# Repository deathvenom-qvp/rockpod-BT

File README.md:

<p align="center">
  
  <h1 align="center">Rockpod</h1>
  <p align="center">
    Custom Rockbox firmware for iPod Classic and iPod Video.<br>
    MFi digital audio, Cover Flow, dynamic colors.
  </p>
  <p align="center">
    
    <br/>
    
  </p>
</p>

---

## About This Fork: USB-C + Bluetooth for iPod Classic and iPod Video

> **Status: planning / early development.** Nothing below is implemented yet. Everything else in this README describes upstream [Rockpod](https://github.com/nuxcodes/rockpod) and still applies.

This fork adds firmware support for a hardware mod. The mod replaces the iPod's 30-pin dock connector with a custom board that carries a USB-C port and a built-in Bluetooth audio transmitter.

### Target iPods

| Model                    | Rockbox target | Notes                                                                 |
| ------------------------ | -------------- | --------------------------------------------------------------------- |
| iPod Classic 7G          | `ipod6g`       | Primary development target                                            |
| iPod Classic 6G / 6.5G   | `ipod6g`       | Same build and chips as 7G; board fit in thick/thin cases to confirm  |
| iPod Video 5G / 5.5G     | `ipodvideo`    | Separate serial shim needed; plastic front allows better antenna range |

The board solders onto the original 30-pin pads. USB, power, audio and control all come from those pads, so there is no other soldering to the logic board. That keeps the install simple and reversible.

### Hardware

| 30-pin pad   | Signal               | Goes to                               |
| ------------ | -------------------- | ------------------------------------- |
| 23, 25, 27   | USB VBUS, D−, D+     | USB-C receptacle (charging + sync)    |
| 18           | 3.3V accessory power | Bluetooth module supply               |
| 12 / 13      | Serial TX / RX       | Bluetooth module UART RX / TX         |
| 3 / 4        | Line out R / L       | Bluetooth module analog input         |
| 2            | Audio ground         | Bluetooth module audio reference      |
| 1, 15, 16, 29, 30 | Ground          | Board ground                          |

- **Bluetooth module:** Feasycom FSC-BT1046 (Qualcomm QCC3056, 12.4 × 12.4 mm, aptX), small enough for a one-piece board. Fallback: FSC-BT1035 (same chip, 26.9 × 13 mm, needs a rigid-flex board). Both are A2DP Source modules controlled by AT commands over UART.
- **Schematic and PCB (v0.1 draft):** [`hardware/pcb`](hardware/pcb) has a KiCad 8 project for EasyEDA Pro import: the full schematic and a placed, not yet routed, 2-layer L-shaped board with every part on top. Two footprints are placeholders until checked against the parts bought.
- **Attach and audio design:** [`hardware/DESIGN.md`](hardware/DESIGN.md). The board solders onto the receptacle's pads: castellated edges on the two shield tabs, and a bottom-side pad row for the signals (only the pins we use), left partly exposed so a fine-tip iron can reflow it. Audio ground (pin 2) stays isolated from GND, and each audio channel runs as a pseudo-differential pair with an RF filter.
- **30-pin reference CAD:** [`hardware/reference/ipod-30pin`](hardware/reference/ipod-30pin) has the receptacle's footprint and symbol for Eagle and KiCad, from SparkFun's library. Still to be checked against a real logic board.
- **Parts list:** [`hardware/BOM.csv`](hardware/BOM.csv), in JLCPCB assembly format. Estimated parts cost is about $12 per board, almost all of it the Bluetooth module.
- **USB-C:** 5.1 kΩ pull-downs on CC1/CC2 so USB-C chargers supply power. Data stays USB 2.0.
- **Antenna:** on the 6G/7G, placed at the dock opening, the only gap in the metal case. On the 5G/5.5G, it can face the plastic front instead.
- **No pairing button.** Pairing is done from the Rockbox menu.
- **One PCB for all models** if measurements confirm the pads line up across the 5G, 6G and 7G. Third-party USB-C boards already fit gen 5–7, which suggests they do.

**To verify on real hardware:**
- The current limit of the 3.3V accessory supply on each power chip.
- That the pad positions match across generations.
- How much room there is behind the connector in each case.

### Planned firmware changes

- **Bluetooth menu.** Replaces *System → Accessory Power Supply*. On/off reuses the existing `accessory_supply` setting, which switches pad 18 and powers the module: PMU LDO6 on the 6G/7G, the PCF50605 on the 5G/5.5G. The config name stays the same, so existing settings files keep working.
- **Shared Bluetooth driver.** The driver and menus live in the app layer, so one implementation serves both targets.
- **Per-target serial shims.** On both targets the dock UART is set up for iAP: it waits for an accessory and auto-detects the baud rate. A new build option will open the port at a fixed 115200 8N1 and send data to the Bluetooth driver instead. That means one shim in `serial-6g.c` (6G/7G) and one in `uart-pp.c` (5G/5.5G). iAP over USB (MFi digital audio) is unaffected.
- **Pairing screens:**
  - Scan for nearby devices, showing name and signal strength.
  - Pair and connect.
  - Manage paired devices (connect or forget).
  - Show live connection status from the module's `+A2DPSTAT` events.
- **Line out follows Bluetooth.** Line out is powered on automatically while Bluetooth is on.
- **Volume from the click wheel.** The QCC transmitter AT command set has `AT+ABSVOL`, which sets the headphones' volume directly, so Rockbox can send its volume to the headphones on every model. The module also reports headphone volume buttons (`+CTVOLUP` / `+CTVOLDN`).
- **Later:** use headphone buttons (AVRCP) to control Rockbox playback.

### Roadmap: hardware first

The priority is one board that drops into every supported iPod. Firmware work starts once the hardware is proven.

1. **Measure.** Pad positions, and the room behind the connector, on a 5G, 6G and 7G logic board and case. Design to the tightest one, the thin 7G.
2. **Confirm the module.** Check with Feasycom that the FSC-BT1046 uses the same QCC transmitter AT command set as the FSC-BT1035, and confirm JLCPCB stock.
3. **Bench test.** Drive the module from a USB-to-serial adapter: scan, pair, connect, line-in audio and absolute volume.
4. **Measure pad 18 under load.** On each iPod, check the 3.3V accessory supply holds up while the module pairs and streams.
5. **Prototype the board** and test the fit, the USB-C charging and sync, and the antenna range inside each case.
6. **Firmware.** Write the Bluetooth driver, the serial shims and the menus.

---

Rockpod is a [Rockbox](https://www.rockbox.org) fork for iPod Classic (6th/7th gen, 2007–2014) and iPod Video (5th/5.5th gen, 2005–2006). It adds MFi digital audio output, a rewritten Cover Flow, dynamic album art colors, and SSD-aware power management.

Rockpod supports both HDD and iFlash-modded units. Both iPod models share the same 320x240 display and get the same UI features — Cover Flow, dynamic colors, themes, and rendering improvements. Hardware-specific features like SSD power management and MFi digital audio are iPod Classic only for now. It's a drop-in replacement for the official Rockbox firmware, with no reformatting or data loss.

---

## Features

### Digital Audio Output
> Supported on iPod Classic 6G/7G

Rockpod is the first open source firmware to support digital audio output over the iPod's dock connector. It handles the full Apple iAP authentication handshake, negotiates sample rate with the accessory, and sends bit-perfect PCM over USB, bypassing the iPod's internal DAC. The entire Rockbox DSP chain (EQ, crossfeed, replaygain) is preserved in the output path.

This works with any MFi iPod dock connector accessory — DACs, speakers, docks, car stereos, and other digital audio accessories built for the iPod.

- **Full iAP/IDPS authentication** — certificate exchange, challenge-response, FID token negotiation, Digital Audio Lingo activation
- **3 MB TX ring buffer** — absorbs codec decode bursts and compensates for I2S/USB clock drift (~44,117 Hz vs 44,100 Hz)
- **Double-buffered ISO IN** — DMA re-arm decoupled from audio pull for glitch-free streaming on docks with HID polling
- **Glitch-free transitions** — fade-in on play, fade-out on pause/underflow, buffer flush between tracks
- **Full DSP chain preserved** — EQ, crossfeed, replaygain, stereo width all apply before the USB stream
- **HP amps auto-mute** — CS42L55 headphone amplifiers power down during USB streaming
- **USB-C compatible** — digital audio output also works with USB-C connector mods

None of this existed in Rockbox before. It required building a new protocol stack from scratch: USB Audio Class 1.0 source mode, Apple's iAP/IDPS authentication (certificate exchange, challenge-response, FID token negotiation), a custom iAP-over-USB-HID transport layer, and Digital Audio Lingo to activate streaming.

<details>
<summary><strong>Compatible devices</strong></summary>

Any iPod dock connector accessory that uses Digital Audio Lingo (0x0A) should work. The OPPO HA-2SE is the primary tested device. DACs, speakers, docks, and car stereos that accept digital audio from an iPod are all expected to be compatible.

**DACs**

- OPPO HA-2 / HA-2SE
- Sony PHA-1 / PHA-1A
- Sony PHA-2 / PHA-2A
- Onkyo DAC-HA200
- Denon DA-10
- JDS Labs C5D
- Fostex HP-P1
- Cypher Labs AlgoRhythm Solo / Solo -dB

**Speakers / Docks** — MFi-certified speakers and docks that use digital audio (not analog line-out) over the dock connector should also work.

</details>

<details>
<summary><strong>Under the hood: signal flow</strong></summary>

```
iPod connects via dock USB
    │
    ├─ USB enumeration: Config 2 = UAC1 source + iAP HID (Apple VID/PID 0x05AC:0x1261)
    │
    ├─ iAP authentication over USB HID:
    │     StartIDPS → SetFIDTokenValues → EndIDPS
    │     → MFi certificate exchange → challenge-response
    │
    ├─ Digital Audio Lingo activation:
    │     GetAccSampleRateCaps → TrackNewAudioAttributes @ 44.1 kHz
    │
    ├─ Accessory selects alt-setting on source streaming interface
    │
    └─ Audio path:
          Codec → DSP (EQ, crossfeed, replaygain)
            → PCM mixer → buffer hook → TX ring buffer
              → double-buffered ISO IN → MFi accessory
```

The iAP HID transport handles multi-report fragmentation for large payloads (128-byte RSA signatures span multiple HID reports, reassembled via link control bytes). Transaction IDs are tracked and echoed for all post-IDPS commands.

Key files:

- `firmware/usbstack/usb_audio.c` — source mode streaming engine
- `firmware/usbstack/usb_iap_hid.c` — iAP-over-USB-HID transport (new)
- `firmware/usbstack/usb_core.c` — dual USB configuration
- `apps/iap/iap-lingo0.c` — IDPS protocol, Digital Audio Lingo
</details>

---

### Cover Flow

Stock PictureFlow shows 3 slides, uses hardcoded colors, and is buried in the plugins menu. Rockpod rewrites the renderer to match Apple's Cover Flow — 7 visible slides w/ uniform tilt angle, custom theme integration, status bar toggle, faster transitions — and promotes it to a top-level menu entry.

<!-- TODO: Add before/after screenshot — stock PictureFlow vs Rockpod Cover Flow -->

|                     Cover Flow                     |                        Full-screen mode                         |
| :------------------------------------------------: | :-------------------------------------------------------------: |
|  |  |
|                   Status bar on                    |                     Status bar toggled off                      |

|                          Track list                          |                      Display settings                       |
| :----------------------------------------------------------: | :---------------------------------------------------------: |
|  |  |
|             Title only — no track number prefix              |                Slide tuck, crossfade, speed                 |

- **Theme-aware colors** — slide edges and backgrounds fade toward your theme's background color, not hardcoded black
- **Status bar support** — integrates with the SBS status bar, showing "Cover Flow" in the title bar. Can be toggled off for full-screen mode
- **7 visible slides w/ parallel slide rendering** — matching Apple's Cover Flow projection
- **Configurable transition speed** — scroll and transition speeds are adjustable in display settings
- **Text crossfade** — album and artist text fades smoothly between slides instead of snapping
- **100-slot slide cache** (up from 64), Bayer-ordered dithering, 1-second background polling in SSD mode
- **Track list** shows title only — no "1.03 -" disc/track number prefixes
- **No startup delay** — the 2-second "Loading..." splash is eliminated under SSD mode

---

### Dynamic Colors

The UI automatically extracts dominant and accent colors from the currently playing album art and applies them across all skinnable screens — menus, status bar, and now playing. Colors fade smoothly over 500 ms when the track changes.

|                                                          |                                                          |
| :------------------------------------------------------: | :------------------------------------------------------: |
|        |        |
|        |        |

- **Album art color extraction** — dominant and accent colors pulled from the current track's artwork
- **Full theme color coverage** — foreground, background, selector bar, selector text, selector gradient, and list separators all adapt
- **Smooth transitions** — 500 ms fade between color palettes on track change
- **Contrast enforcement** — accent colors are pushed brighter or darker if insufficient contrast against the dominant color
- **On by default** — can be toggled off under Theme Settings

---

### Storage Mode
> Supported on iPod Classic 6G/7G

Rockpod works with both stock HDDs and iFlash SSD mods. HDD behavior is unchanged from stock Rockbox. When an SSD is detected, Rockpod switches to a lighter sleep strategy — faster wake times, lower idle power draw, and no unnecessary spin-up delays.

| Storage Mode                                         |
| :--------------------------------------------------- |
|  |
| Auto-detect, or manually select HDD / SSD            |

- **Auto-detection** via ATA IDENTIFY heuristics (rotation rate, form factor, TRIM support, CFA compliance)
- **Two-phase idle sleep** — clock-gate after 7 seconds (near-instant wake), then cut AUTOLDO after 30 seconds with backlight off
- **Instant wake from clock-gate** — no bus reset, no re-identify (<5 ms)
- **Pre-wake on backlight** — storage wakes when the screen turns on, ready before you navigate
- **HDD features bypassed** — APM and AAM skipped for SSDs
- **Plugin splash skipped** — no "Loading..." screen when load times are negligible

<details>
<summary><strong>Under the hood: sleep states</strong></summary>

| State           | What happens                                  | Wake time |
| --------------- | --------------------------------------------- | --------- |
| **Active**      | Normal operation                              | —         |
| **Clock-gated** | ATA clock off, flash powered, GPIOs held      | <5 ms     |
| **Deep sleep**  | AUTOLDO cut, GPIOs tri-stated, controller off | ~330 ms   |

Stock HDD behavior: full power-down + re-init at ~530 ms.

Key file: `firmware/target/arm/s5l8702/ipod6g/storage_ata-6g.c`

</details>

---

### Power Management
> Supported on iPod Classic 6G/7G

- **I2S clock gating** — bus clock gated when no audio is playing
- **Codec idle power-down** — CS42L55 enters PDN_CODEC on idle, pop-free resume (master mute → power-down → 200 us settle → unmute)
- **Smart charger detection** — LTC4066 `!CHRG` pin sampled with backlight-gated timing and 500 ms settle to distinguish real chargers from weak USB sources like MFi accessories
- **Charge gate** — GPIO C1 blocks battery charging when USB can't deliver 500 mA, preventing accessory battery drain
- **Auto-poweroff with USB** — device shuts down after idle timeout even with non-charging USB connected (stock blocks poweroff indefinitely on any USB)
- **iAP idle tick** — polling drops from 10 Hz to 1 Hz after auth, saving ~9 CPU wakeups/sec

<details>
<summary><strong>Under the hood: LTC4066 charge control</strong></summary>

| GPIO      | Function          | Rockpod behavior                       |
| --------- | ----------------- | -------------------------------------- |
| B6 (HPWR) | USB current limit | LOW = 100 mA, HIGH = 500 mA            |
| B7 (SUSP) | USB suspend       | Prevents any USB power draw            |
| C1        | Charge disable    | HIGH blocks charging from weak sources |

When connected to an MFi accessory without a power bank, C1 goes HIGH during backlight-off to block trickle drain. On backlight-on, C1 goes LOW to sample `!CHRG` — if charging is detected, it stays LOW.

Key files: `firmware/target/arm/s5l8702/ipod6g/power-6g.c`, `powermgmt-6g.c`

</details>

---

### Menu

All standard Rockbox menu items are available.

|                     Main menu                     |                    Database track list                     |
| :-----------------------------------------------: | :--------------------------------------------------------: |
|  |  |
|       Full menu available, shown customized        |         Title only — no disc/track number clutter          |

---

### Improved UI Rendering

- **Scroll-to-start flash eliminated** — custom themes with scrolling text in the main menu would flash or flicker when the scroll position reset to the start. Rockpod fixes the viewport rendering order to prevent this, making themed menus render cleanly without visual artifacts.
- **Track name cleanup** — strips the "01 " numeric prefix that iTunes sync adds to filenames, so tracks display by their actual title across Cover Flow, Database, and WPS

---

### Bundled Themes

The repo includes third-party themes under `themes/`:

- **adwaitapod_dark_simplified** — modified with swapped play/pause button icons. Original by [Dook](https://github.com/D0-0K/adwaitapod) (CC-BY-SA). Theme zip available in the [v2.0 release](https://github.com/nuxcodes/rockpod/releases/tag/v2.0).
- **Themify 2** — modified with corrected menu text centering. Original by [Dook](https://github.com/D0-0K/themify).

---

## Supported Models

| Feature                   | iPod Classic (6G/7G)  | iPod Video (5G/5.5G) |
| ------------------------- | --------------------- | -------------------- |
| **MFi digital audio**     | Yes                   | Planned              |
| **Cover Flow**            | Yes                   | Yes                  |
| **Dynamic Colors**        | Yes                   | Yes                  |
| **UI improvements**       | Yes                   | Yes                  |
| **Themes**                | Yes (320x240)         | Yes (320x240)        |
| **SSD power management**  | Yes                   | No                   |
| **Advanced power mgmt**   | Yes                   | No                   |

## At a Glance

|                         | Stock Rockbox                           | Rockpod                                        |
| ----------------------- | --------------------------------------- | ---------------------------------------------- |
| **MFi digital audio**   | Not supported                           | DACs, speakers, docks — Classic only           |
| **Dynamic colors**      | Not supported                           | Album art color extraction with smooth fades   |
| **Cover Flow**          | 3 slides, no status bar, 70-degree tilt | 7 slides, status bar, parallel projection      |
| **SSD idle**            | Full power-down, ~530 ms wake           | Clock-gate, <5 ms wake — Classic only          |
| **Codec power**         | Always on                               | Auto power-down on idle — Classic only         |
| **USB power**           | Charges from any USB source             | Smart charge gating — Classic only             |
| **Auto-poweroff + USB** | Blocked indefinitely                    | Works for non-charging accessories — Classic only |

---

## Installation

> **Prerequisite:** Your iPod must already have the Rockbox bootloader installed. See the [Rockbox installation guide](https://www.rockbox.org/wiki/RockboxUtility) if needed.

1. Download the correct zip from [Releases](https://github.com/nuxcodes/rockpod/releases/latest):
   - `rockbox-ipod6g.zip` for iPod Classic (6G/7G)
   - `rockbox-ipodvideo-5g.zip` for iPod Video (5G/5.5G)
2. Connect your iPod in disk mode
3. Extract the zip to the root of the iPod (creates/updates `.rockbox`)
4. Eject and reboot

PictureFlow rebuilds its album art cache on first launch after upgrade. This is automatic.

---

## Building from Source

```bash
# iPod Classic 6G (default, clean build)
./build-hw.sh

# iPod Video 5G (clean build)
./build-hw.sh 5g

# Incremental rebuild
cd build-hw-ipod6g && make -j$(sysctl -n hw.ncpu) && make zip
cd build-hw-ipodvideo && make -j$(sysctl -n hw.ncpu) && make zip

# Simulator (6G)
./build-sim.sh
cd build-sim && ./rockboxui
```

`build-hw.sh` accepts `ipod6g` / `6g` (default) or `ipodvideo` / `5g`. Output goes to `build-hw-<target>/`. Cross-compiler toolchains: `tools/rockboxdev.sh`.

---

## Roadmap

**iPod Video 5G/5.5G MFi digital audio.** Master supports serial iAP and analog line-out on iPod Video, but does not advertise Digital Audio because its USB audio transport is not enabled. The experimental USB work remains on the separate `ipod5g-mfi-usb` branch.

**Generic USB audio support via host mode.** The current support uses USB device mode — the accessory is the host and the iPod authenticates as an Apple audio source. This only works with iPod MFi accessories. The next step is USB host mode, where the iPod becomes the host and sends audio to any class-compliant UAC device — standard USB-C DAC dongles via a dock-to-OTG adapter. The S5L8702's DWC OTG controller supports host mode in hardware; the work is in the host stack and UAC class driver.

---

## Known Limitations

- **iPod MFi accessories only** — generic UAC sinks not yet supported (see Roadmap)
- **16-bit PCM, 44.1 / 48 kHz** — USB Audio Class 1.0 ceiling
- **iPod Classic and iPod Video only** — untested on other Rockbox targets
- **No USB DAC (sink) mode** — USB audio config is repurposed for digital audio output
- **Rockbox bootloader required** — needs an existing Rockbox installation

---

## Credits

Built on the work of the [Rockbox](https://www.rockbox.org/) project and its contributors.

- **Themes:** adwaitapod_dark_simplified and Themify 2 by [Dook](https://github.com/D0-0K) (CC-BY-SA)
- **MFi reference:** [ipod-gadget](https://github.com/oandrew/ipod-gadget) descriptor layout, [rockbox-mojyack](https://github.com/mojyack/rockbox) iPod 5G iAP implementation, Apple MFi Accessory Firmware Specification

## License

[GNU General Public License v2.0](https://www.gnu.org/licenses/old-licenses/gpl-2.0.html)

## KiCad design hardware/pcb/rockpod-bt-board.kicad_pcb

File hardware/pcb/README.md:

# Unified board v0.1: schematic and first-pass layout

KiCad 8 project for EasyEDA Pro import: the complete schematic and a placed (not yet routed) 2-layer PCB. All parts are SMD on the top side. The underside carries only the pads that solder to the iPod.

> **Draft for review, not for ordering.** Two footprints are placeholders (see "Assumptions"), and the geometry has to be checked against measured iPods (roadmap step 1). Routing comes after both are settled.

## Files

| File | What it is |
| --- | --- |
| `rockpod-bt-board.kicad_sch` | Full schematic. Nets connect by label name. Every part has an `LCSC` / `Supplier Part` field. |
| `rockpod-bt-board.kicad_pcb` | Board outline, placed footprints with nets (ratsnest), iPod interface pads, shield tabs, alignment holes, top GND pour and antenna keep-out. |
| `rockpod-bt-board.kicad_pro` | Project file. |
| `board-preview.png` | Plot of the placement. |
| `tools/` | Python generator. Edit `design.py` (geometry, parts, placement) and rerun to regenerate everything. |

## Importing into EasyEDA Pro

1. *File → Import → KiCad*, and select `rockpod-bt-board.kicad_pro` (or the `.kicad_sch` and `.kicad_pcb`).
2. **Replace U1 and J1 with EasyEDA library parts:**
   - U1: search `C9900132912` (FSC-BT1046).
   - J1: search `C5187472` (SHOU HAN TYPE-C 16P QTWT).

   Then *Update PCB from schematic*. Every other footprint is a standard 0402, 0603, SOT-23-6 or 1206 land pattern.
3. Check the board against the "Assumptions" list, then route with the rules below.

## Board

- **2 layers, 0.8 mm FR4.** 36.5 × 20.8 mm, L-shaped.
- **Main strip** sits in the 30-pin receptacle's place. It carries the USB-C port, USB ESD protection, the CC resistors and the audio front end.
- **Extension** reaches back into the case on one side only, as decided, to stay clear of the logic board's other connectors. It carries the Bluetooth module, its supply parts, the RF filter and the antenna. Everything sits in `design.py`, so it can be mirrored to the other side once the iPods are measured.
- **Rear edge over the pad row** stops 0.125 mm past the pad centreline, leaving the rear 0.75 mm of each iPod pad exposed for a fine-tip iron.
- **Underside pads run flush to that rear edge** (0.28 × 1.0 mm), so solder flows straight from the exposed iPod pad onto ours. This breaks the usual 0.2 mm copper-to-edge rule on purpose:
  - Mark it as accepted in EasyEDA's DRC.
  - Add an order note for JLCPCB not to trim the bottom pads on the rear edge.
- **Shield tabs:** tab 31 (left) is castellated on the board edge. Tab 32 (right) falls inside the extension, so it gets a plated slot instead, which solder fed from the top flows through.
- **Alignment holes:** two 1.1 mm holes match the iPod's receptacle locating holes at x = ±6.25 mm.
- **Antenna (internal, ceramic chip, in the dock opening):** the module has no antenna of its own. The FSC-BT1046 datasheet says to connect a 50 Ω antenna to RF_IO (pin 7).
  - **Placement:** ANT1, a 3.2 × 1.6 mm ceramic chip, sits at the front edge beside the USB-C, inside the old 30-pin opening. On the 6G/7G that opening, behind the plastic bezel insert, is the only gap in the metal case.
  - **Keep-out:** an area of about 5 × 3 mm around ANT1 has no copper on either layer.
  - **Matching:** the pi-match sits right beside the antenna. R9 is fitted with 0 Ω; C10 and C11 are left unfitted for tuning.
  - **Feed line:** RF_MOD runs from module pin 7 to the pi-match as a 50 Ω coplanar line.
  - **Watch:** the iPod logic board under the old receptacle may carry a ground plane right below the antenna, which will detune it. Plan to tune C10/C11 with the board installed.

## Assumptions to check first

1. **U1 pin 1 position.** The FSC-BT1046 datasheet's text gives the pin table, the 1.0 mm pitch and the 12.4 mm body, but not where pin 1 sits. This footprint assumes pin 1 at the front-left corner, numbered counter-clockwise. The EasyEDA library footprint for C9900132912 settles it, and parts around the module may need to move once it's in.
2. **J1 is the SHOU HAN TYPE-C 16P QTWT (C5187472):** a 16-pin USB-C receptacle that LCSC lists as fully surface-mount, with no through-hole shell legs, 7.35 mm long. It replaces the HRO TYPE-C-31-M-12 and G-Switch GT-USB-7010ASV, which both have through-hole shell legs. The J1 footprint here is a generic 16-pin pattern, so use the EasyEDA library footprint.
3. **USB-C depth.** A USB-C receptacle is about 7.35 mm long. The 30-pin body was about 6.6 mm deep, and the board can't run past the pad row. So the USB-C mouth sits 0.45 mm proud of the board front, about 0.6 mm past where the 30-pin mouth was. Check that against the case opening.
4. **Case clearance.** Check the extension (x = 9 to 24.8 mm, y up to 14 mm behind the pad row) against parts on the logic board and the curve of the case corner.
5. **Pad positions.** The iPod pad row comes from SparkFun's footprint. The contact row in the 3D model in `../reference/ipod-30pin/3d` agrees: 30 tails at 0.5 mm pitch, centred ±7.25 mm.
6. **Shield tabs are ground,** on each generation.

## Routing rules

- **AGND (iPod pin 2) never touches GND.** Keep it off the ground pour. It splits into two return traces, one for each audio pair.
- **Audio pairs:**
  - Route LINE_L/AGND → R5/R6 → C6/C7 → AUD_L_P/AUD_L_N, and LINE_R/AGND → R7/R8 → C8/C9 → AUD_R_P/AUD_R_N, as tightly coupled pairs of about equal length, each pair kept apart from the other.
  - C12 and C13 go right at the module pins.
  - Keep the pairs away from USB D+/D−, RF_MOD/RF_ANT and the antenna.
- **USB D+/D−:** a 90 Ω differential pair from J1 through U2 to the iPod pads 25/27, kept short.
- **iPod interface pads (underside):** USB-C pads sit directly above several of them. Fan the bottom pads out on the bottom layer first, then via up to the top clear of J1's pads. Vias under the USB-C body must be tented.
- **Underside copper:** don't pour on the bottom layer, since it sits on the iPod logic board. Keep bottom traces short and under solder mask.
- **RF:** RF_MOD from module pin 7 to C10/R9/C11 beside the antenna, as a 50 Ω coplanar line over the top ground pour, stitched with GND vias. Keep it clear of the audio pairs and USB D+/D−. No copper of either layer inside the antenna keep-out.
- **Power:** VACC (pad 18) to C1/C2 (bulk) and C3 (VBAT) / C4 (PIO_POWER) close to the module pins.
- **Checks after soldering:** see `../DESIGN.md`.

## Regenerating

```bash
cd hardware/pcb/tools
python3 gen.py ..                      # writes the .kicad_sch / .kicad_pcb / .kicad_pro, prints clearance checks
python3 validate.py ..                 # parses the files, cross-checks schematic vs PCB nets
python3 render.py ../board-preview.png
```

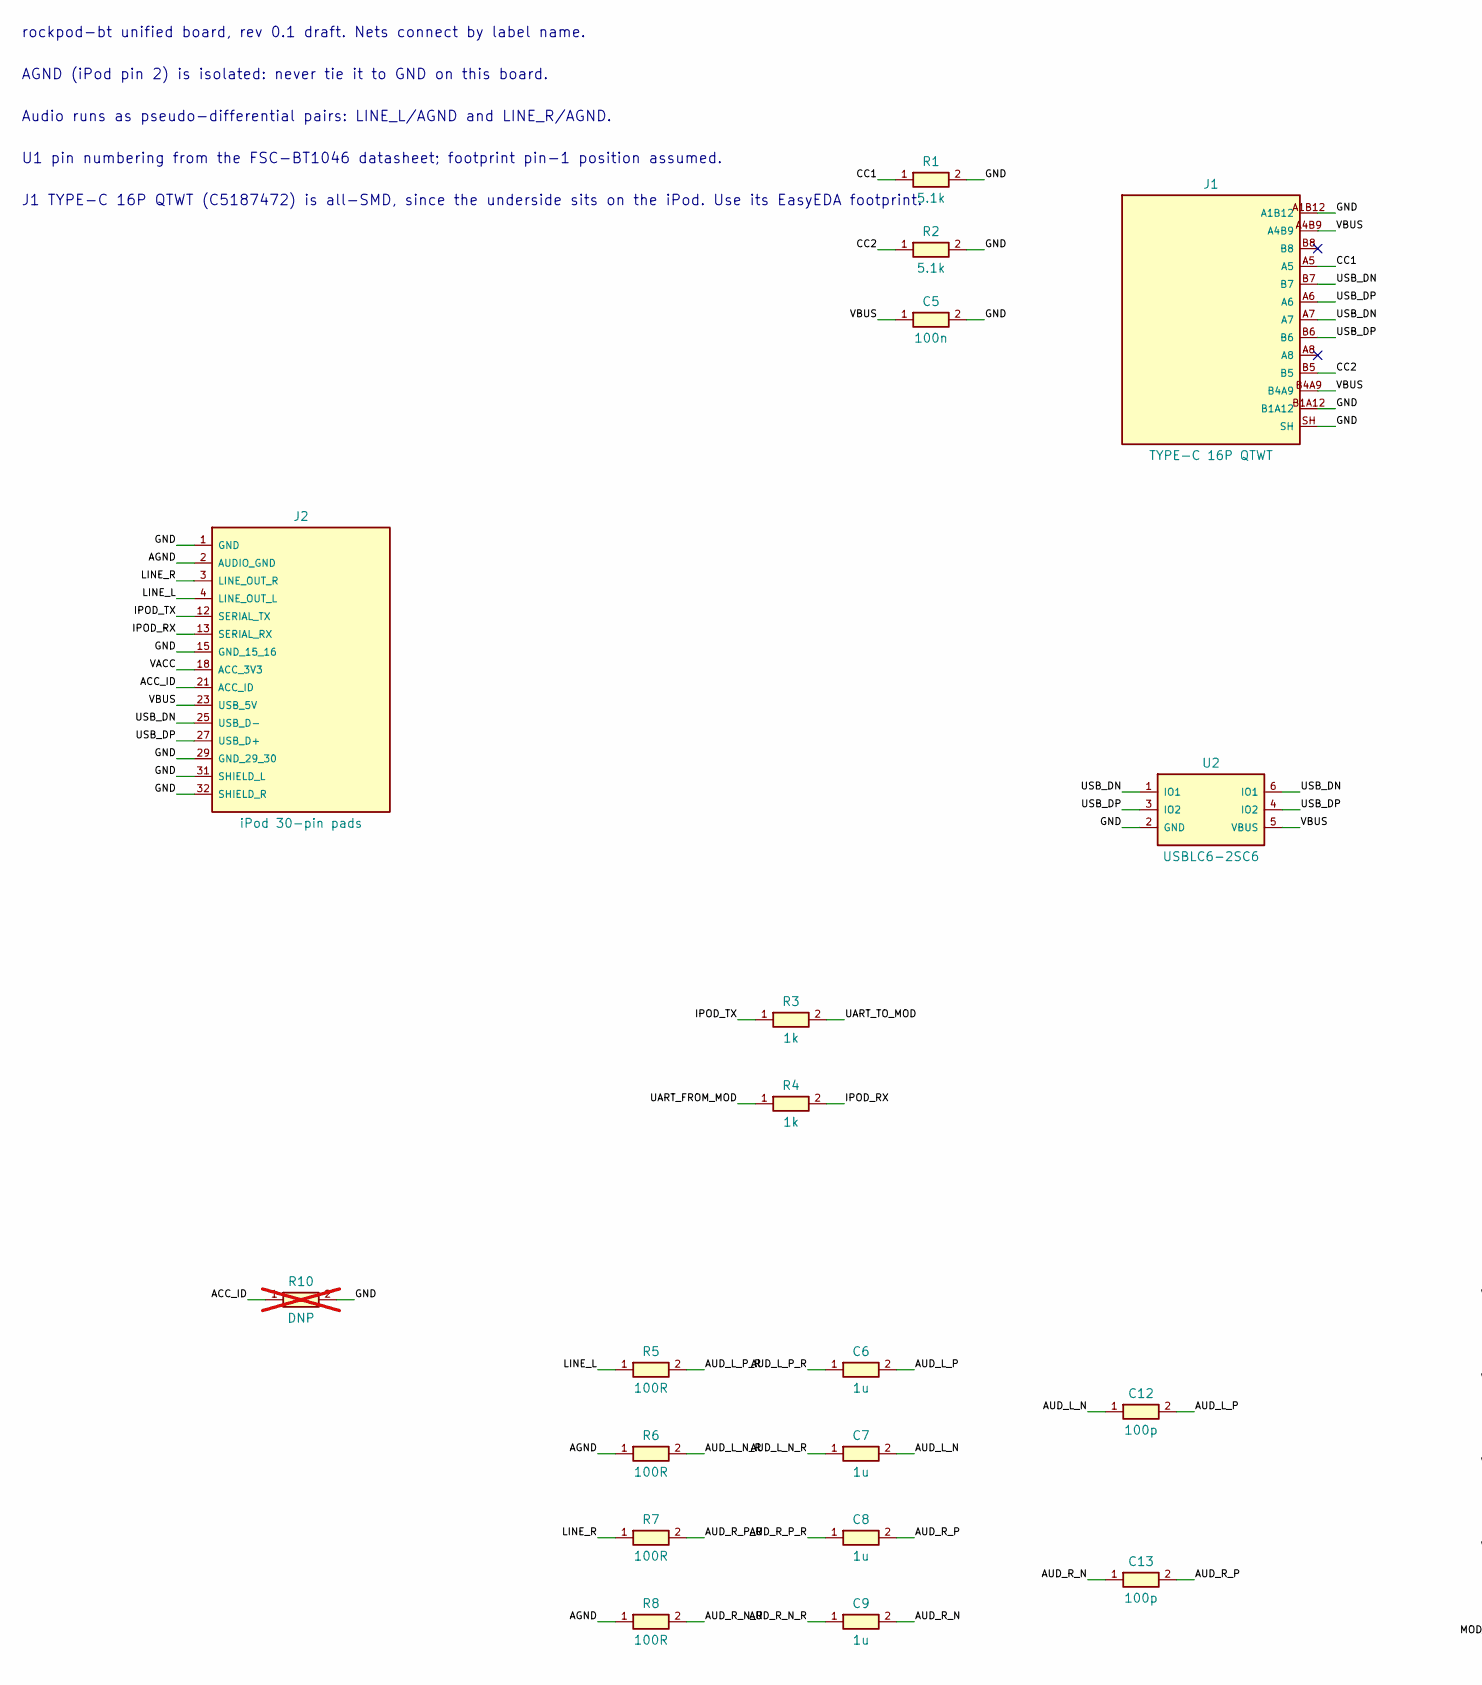
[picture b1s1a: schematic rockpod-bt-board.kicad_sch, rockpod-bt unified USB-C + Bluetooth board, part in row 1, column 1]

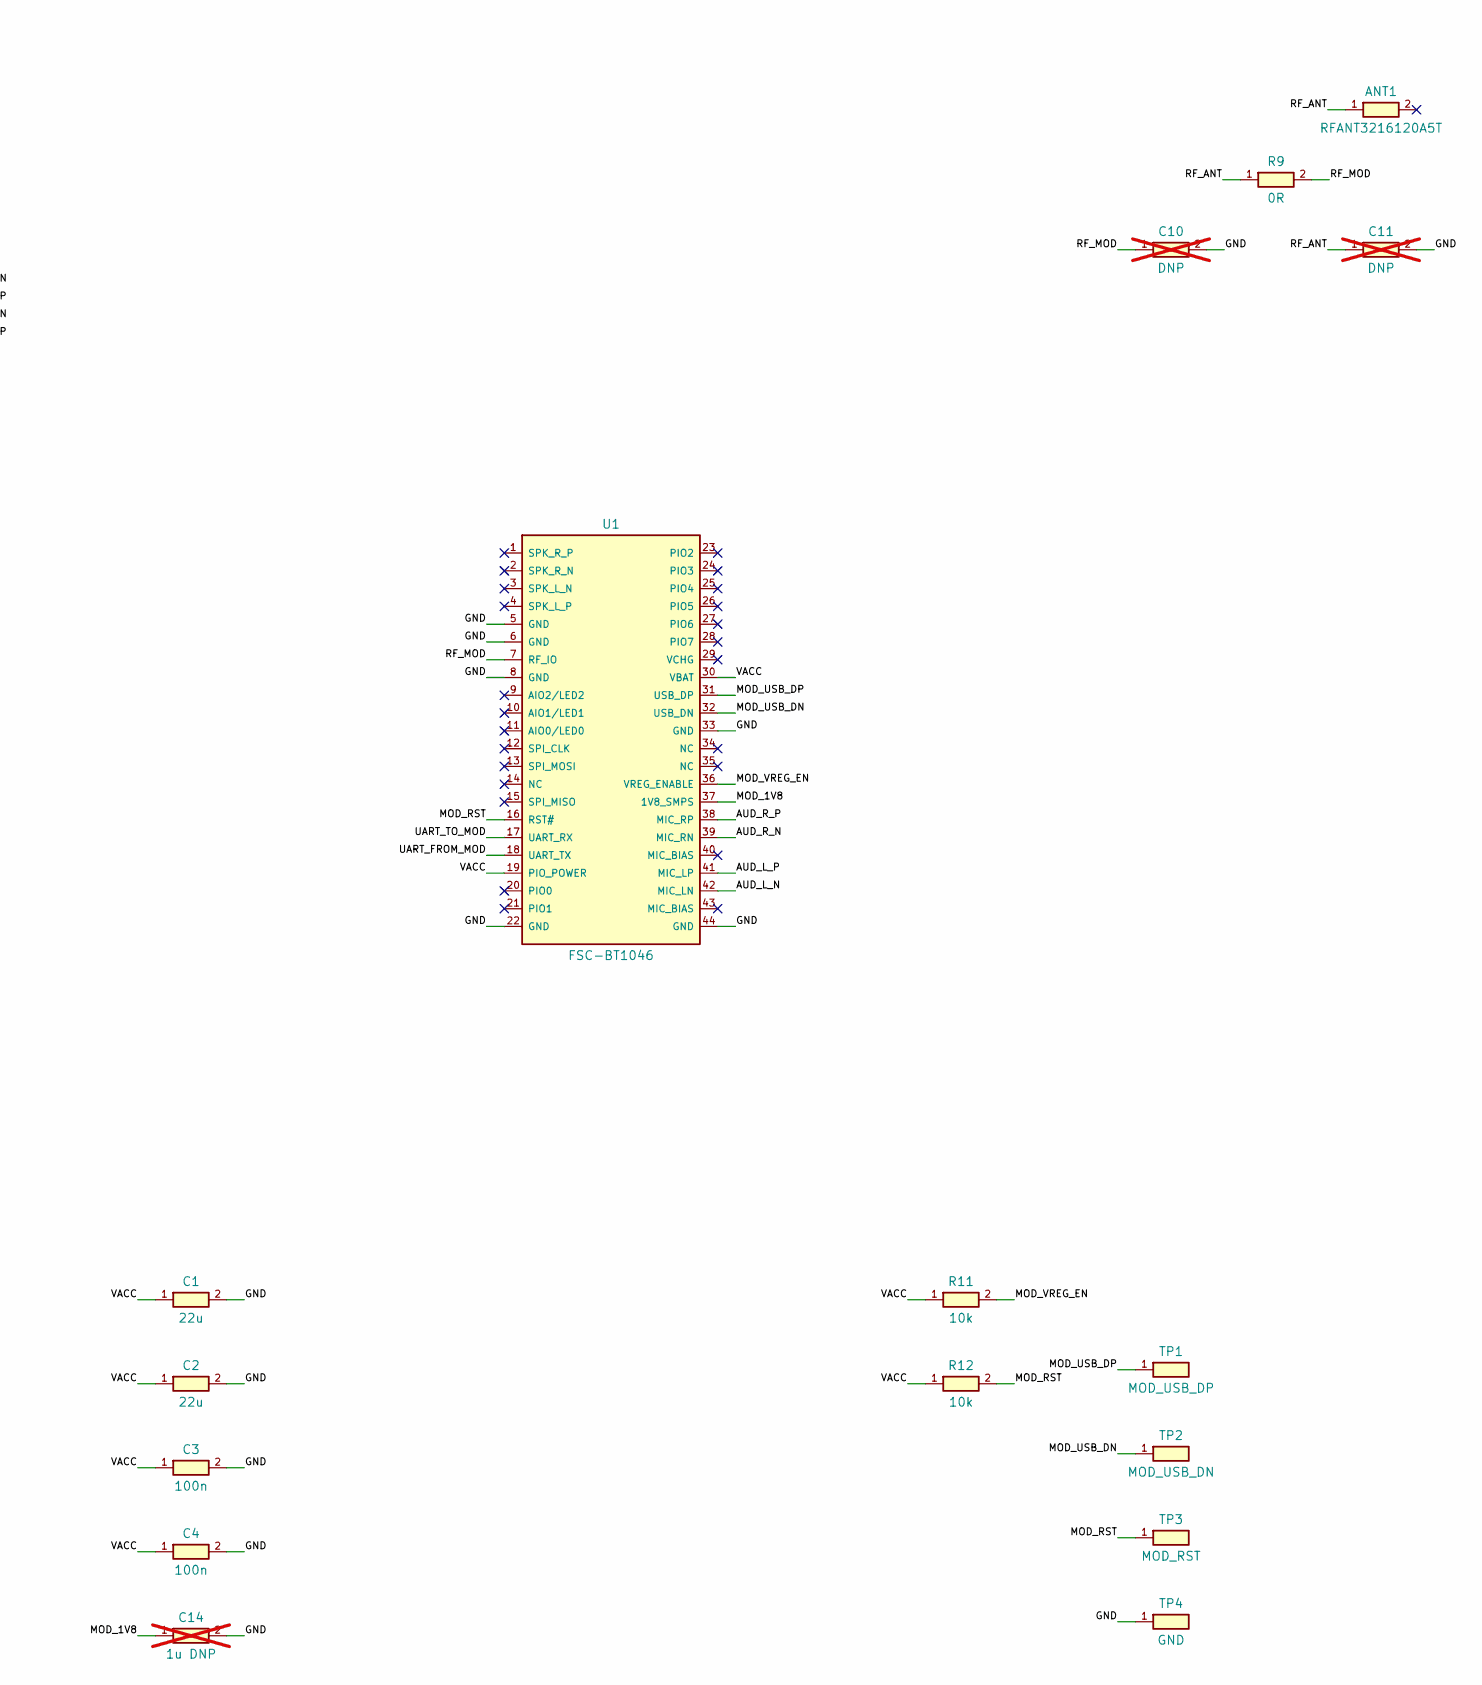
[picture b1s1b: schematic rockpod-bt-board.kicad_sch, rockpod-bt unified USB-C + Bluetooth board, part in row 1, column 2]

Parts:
ANT1: RFANT3216120A5T; ANT_1206; MPN RFANT3216120A5T; LCSC C127629
C1, C2: 22u; 0603; MPN CL10A226MQ8NRNC; LCSC C59461
C3, C4, C5: 100n; 0402; MPN CL05B104KB54PNC; LCSC C307331
C6, C7, C8, C9: 1u; 0402; MPN CL05A105KA5NQNC; LCSC C52923
C10, C11: DNP; 0402; MPN tune; not fitted
C12, C13: 100p; 0402; MPN 0402CG101J500NT; LCSC C1546
C14: 1u DNP; 0402; MPN CL05A105KA5NQNC; LCSC C52923; not fitted
J1: TYPE-C 16P QTWT; USB_C_16P_SMD; MPN TYPE-C 16P QTWT; LCSC C5187472
J2: iPod 30-pin pads; IPOD_IF
R1, R2: 5.1k; 0402; MPN 0402WGF5101TCE; LCSC C25905
R3, R4: 1k; 0402; MPN 0402WGF1001TCE; LCSC C11702
R5, R6, R7, R8: 100R; 0402; MPN 0402WGF1000TCE; LCSC C25076
R9: 0R; 0402; MPN 0402WGF0000TCE; LCSC C17168
R10: DNP; 0402; MPN value TBD; not fitted
R11, R12: 10k; 0402; MPN 0402WGF1002TCE; LCSC C25744
TP1: MOD_USB_DP; TP_1MM
TP2: MOD_USB_DN; TP_1MM
TP3: MOD_RST; TP_1MM
TP4: GND; TP_1MM
U1: FSC-BT1046; FSC_BT1046; MPN FSC-BT1046; LCSC C9900132912
U2: USBLC6-2SC6; SOT-23-6; MPN USBLC6-2SC6; LCSC C7519

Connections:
ACC_ID: J2.21 (ACC_ID), R10.1
AGND: J2.2 (AUDIO_GND), R6.1, R8.1
AUD_L_N: C7.2, C12.1, U1.42 (MIC_LN)
AUD_L_N_R: C7.1, R6.2
AUD_L_P: C6.2, C12.2, U1.41 (MIC_LP)
AUD_L_P_R: C6.1, R5.2
AUD_R_N: C9.2, C13.1, U1.39 (MIC_RN)
AUD_R_N_R: C9.1, R8.2
AUD_R_P: C8.2, C13.2, U1.38 (MIC_RP)
AUD_R_P_R: C8.1, R7.2
CC1: J1.A5, R1.1
CC2: J1.B5, R2.1
GND: C1.2, C2.2, C3.2, C4.2, C5.2, C10.2, C11.2, C14.2, J1.A1B12, J1.B1A12, J1.SH, J2.1 (GND), J2.15 (GND_15_16), J2.29 (GND_29_30), J2.31 (SHIELD_L), J2.32 (SHIELD_R), R1.2, R2.2, R10.2, TP4.1, U1.5 (GND), U1.6 (GND), U1.8 (GND), U1.22 (GND), U1.33 (GND), U1.44 (GND), U2.2 (GND)
IPOD_RX: J2.13 (SERIAL_RX), R4.2
IPOD_TX: J2.12 (SERIAL_TX), R3.1
LINE_L: J2.4 (LINE_OUT_L), R5.1
LINE_R: J2.3 (LINE_OUT_R), R7.1
MOD_1V8: C14.1, U1.37 (1V8_SMPS)
MOD_RST: R12.2, TP3.1, U1.16 (RST#)
MOD_USB_DN: TP2.1, U1.32 (USB_DN)
MOD_USB_DP: TP1.1, U1.31 (USB_DP)
MOD_VREG_EN: R11.2, U1.36 (VREG_ENABLE)
RF_ANT: ANT1.1, C11.1, R9.1
RF_MOD: C10.1, R9.2, U1.7 (RF_IO)
UART_FROM_MOD: R4.1, U1.18 (UART_TX)
UART_TO_MOD: R3.2, U1.17 (UART_RX)
USB_DN: J1.A7, J1.B7, J2.25 (USB_D-), U2.1 (IO1), U2.6 (IO1)
USB_DP: J1.A6, J1.B6, J2.27 (USB_D+), U2.3 (IO2), U2.4 (IO2)
VACC: C1.1, C2.1, C3.1, C4.1, J2.18 (ACC_3V3), R11.1, R12.1, U1.19 (PIO_POWER), U1.30 (VBAT)
VBUS: C5.1, J1.A4B9, J1.B4A9, J2.23 (USB_5V), U2.5 (VBUS)

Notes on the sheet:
rockpod-bt unified board, rev 0.1 draft. Nets connect by label name.
AGND (iPod pin 2) is isolated: never tie it to GND on this board.
Audio runs as pseudo-differential pairs: LINE_L/AGND and LINE_R/AGND.
U1 pin numbering from the FSC-BT1046 datasheet; footprint pin-1 position assumed.
J1 TYPE-C 16P QTWT (C5187472) is all-SMD, since the underside sits on the iPod. Use its EasyEDA footprint.

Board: 2 copper layers, 35 parts (0 on the bottom side), 30 nets, no tracks yet.

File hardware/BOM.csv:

Comment,Designator,Footprint,LCSC Part #,Quantity,MPN,Manufacturer,Notes
USB-C receptacle 16P all-SMD,J1,TYPE-C 16P QTWT,C5187472,1,TYPE-C 16P QTWT,SHOU HAN,Full SMD (no through-hole shell legs); 7.35 mm long; 5000 mating cycles
Bluetooth audio TX module QCC3056,U1,FSC-BT1046 (44-pin stamp),C9900132912,1,FSC-BT1046,Feasycom,JLCPCB-sourced; confirm stock and AT command set first. Fallback: FSC-BT1035 C9900057927 (needs rigid-flex)
USB ESD protection,U2,SOT-23-6L,C7519,1,USBLC6-2SC6,STMicroelectronics,
5.1k 1% CC pull-down,"R1,R2",0402,C25905,2,0402WGF5101TCE,UNI-ROYAL,
1k 1% UART series,"R3,R4",0402,C11702,2,0402WGF1001TCE,UNI-ROYAL,
100R audio series (RF filter),"R5,R6,R7,R8",0402,C25076,4,0402WGF1000TCE,UNI-ROYAL,One per leg of each audio pair; fit 0R (C17168) to bypass the filter
22uF 6.3V X5R bulk,"C1,C2",0603,C59461,2,CL10A226MQ8NRNC,Samsung Electro-Mechanics,
100nF 50V X7R decoupling,"C3,C4,C5",0402,C307331,3,CL05B104KB54PNC,Samsung Electro-Mechanics,
1uF 25V X5R line-in DC block,"C6,C7,C8,C9",0402,C52923,4,CL05A105KA5NQNC,Samsung Electro-Mechanics,Pseudo-differential: L-/R- legs from pad 2 (AGND)
100pF 50V C0G RF filter across each audio pair,"C12,C13",0402,C1546,2,0402CG101J500NT,FH,At the module input pins
0R antenna series (pi match),R9,0402,C17168,1,0402WGF0000TCE,UNI-ROYAL,Module needs an external antenna (RF_IO pin 7)
2.4GHz chip antenna,ANT1,1206,C127629,1,RFANT3216120A5T,Walsin,Alt: C2916136 Rainsun AN3216-245
10k pull-up (VREG_ENABLE / RST#),"R11,R12",0402,C25744,2,0402WGF1002TCE,UNI-ROYAL,
